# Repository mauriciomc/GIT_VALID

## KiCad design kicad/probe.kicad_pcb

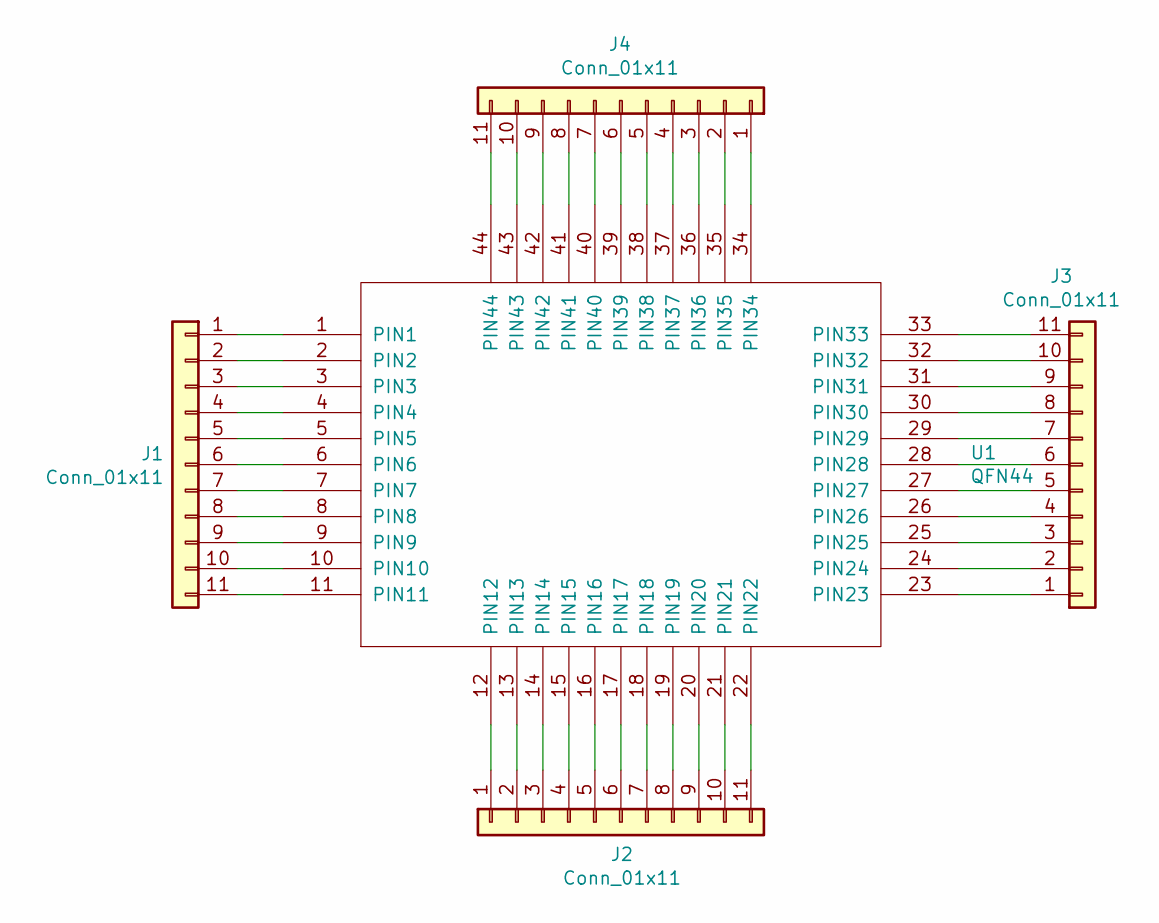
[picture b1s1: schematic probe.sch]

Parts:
J1, J2, J3, J4: Conn_01x11
U1: QFN44; MODULE

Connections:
unnamed: J1.1, U1.1 (PIN1)
unnamed: J1.2, U1.2 (PIN2)
unnamed: J1.3, U1.3 (PIN3)
unnamed: J1.4, U1.4 (PIN4)
unnamed: J1.5, U1.5 (PIN5)
unnamed: J1.6, U1.6 (PIN6)
unnamed: J1.7, U1.7 (PIN7)
unnamed: J1.8, U1.8 (PIN8)
unnamed: J1.9, U1.9 (PIN9)
unnamed: J1.10, U1.10 (PIN10)
unnamed: J1.11, U1.11 (PIN11)
unnamed: J2.1, U1.12 (PIN12)
unnamed: J2.2, U1.13 (PIN13)
unnamed: J2.3, U1.14 (PIN14)
unnamed: J2.4, U1.15 (PIN15)
unnamed: J2.5, U1.16 (PIN16)
unnamed: J2.6, U1.17 (PIN17)
unnamed: J2.7, U1.18 (PIN18)
unnamed: J2.8, U1.19 (PIN19)
unnamed: J2.9, U1.20 (PIN20)
unnamed: J2.10, U1.21 (PIN21)
unnamed: J2.11, U1.22 (PIN22)
unnamed: J3.1, U1.23 (PIN23)
unnamed: J3.2, U1.24 (PIN24)
unnamed: J3.3, U1.25 (PIN25)
unnamed: J3.4, U1.26 (PIN26)
unnamed: J3.5, U1.27 (PIN27)
unnamed: J3.6, U1.28 (PIN28)
unnamed: J3.7, U1.29 (PIN29)
unnamed: J3.8, U1.30 (PIN30)
unnamed: J3.9, U1.31 (PIN31)
unnamed: J3.10, U1.32 (PIN32)
unnamed: J3.11, U1.33 (PIN33)
unnamed: J4.1, U1.34 (PIN34)
unnamed: J4.2, U1.35 (PIN35)
unnamed: J4.3, U1.36 (PIN36)
unnamed: J4.4, U1.37 (PIN37)
unnamed: J4.5, U1.38 (PIN38)
unnamed: J4.6, U1.39 (PIN39)
unnamed: J4.7, U1.40 (PIN40)
unnamed: J4.8, U1.41 (PIN41)
unnamed: J4.9, U1.42 (PIN42)
unnamed: J4.10, U1.43 (PIN43)
unnamed: J4.11, U1.44 (PIN44)

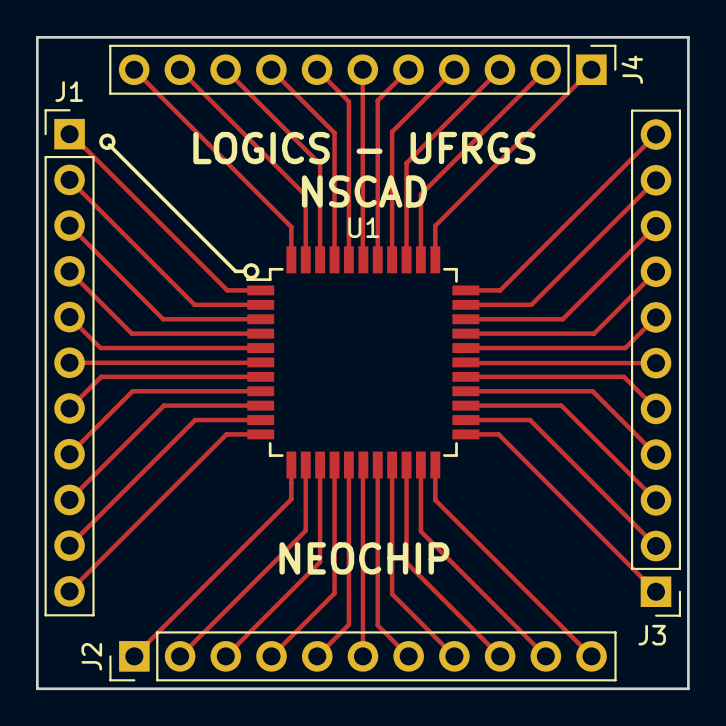
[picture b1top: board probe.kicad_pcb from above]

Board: 2 copper layers, 36.2 x 36.2 mm, 5 parts (0 on the bottom side), 44 nets.

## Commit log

2019-03-29 Initial commit including kicad design files
2019-03-29 Initial commit including design files
2019-04-26 LAYOUT: Modified U1 footprint
